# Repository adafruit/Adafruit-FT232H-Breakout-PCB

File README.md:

## Adafruit FT232H Breakout PCB
<a href="http://www.adafruit.com/products/2264"><br/>
Click here to purchase one from the Adafruit shop</a>

Wouldn't it be cool to drive a tiny OLED display, read a color sensor, or even just flash some LEDs directly from your computer?  Sure you can program an Arduino or Trinket to talk to these devices and your computer, but why can't your computer just talk to those devices and sensors itself?  Well, now your computer can talk to devices using the Adafruit FT232H breakout board!

What can the FT232H chip do?  This chip from FTDI is similar to their USB to serial converter chips but adds a 'multi-protocol synchronous serial engine' which allows it to speak many common protocols like SPI, I2C, serial UART, JTAG, and more!  There's even a handful of digital GPIO pins that you can read and write to do things like flash LEDs, read switches or buttons, and more.  The FT232H breakout is like adding a little swiss army knife for serial protocols to your computer!

PCB files for the Adafruit FT232H Breakout. The format is EagleCAD schematic and board layout
- http://www.adafruit.com/products/2264

### License

Adafruit invests time and resources providing this open source design, please support Adafruit and open-source hardware by purchasing products from [Adafruit](https://www.adafruit.com)!

All text above must be included in any redistribution

Designed by Limor Fried/Ladyada for Adafruit Industries.
Creative Commons Attribution/Share-Alike, all text above must be included in any redistribution. 
See license.txt for additional information.

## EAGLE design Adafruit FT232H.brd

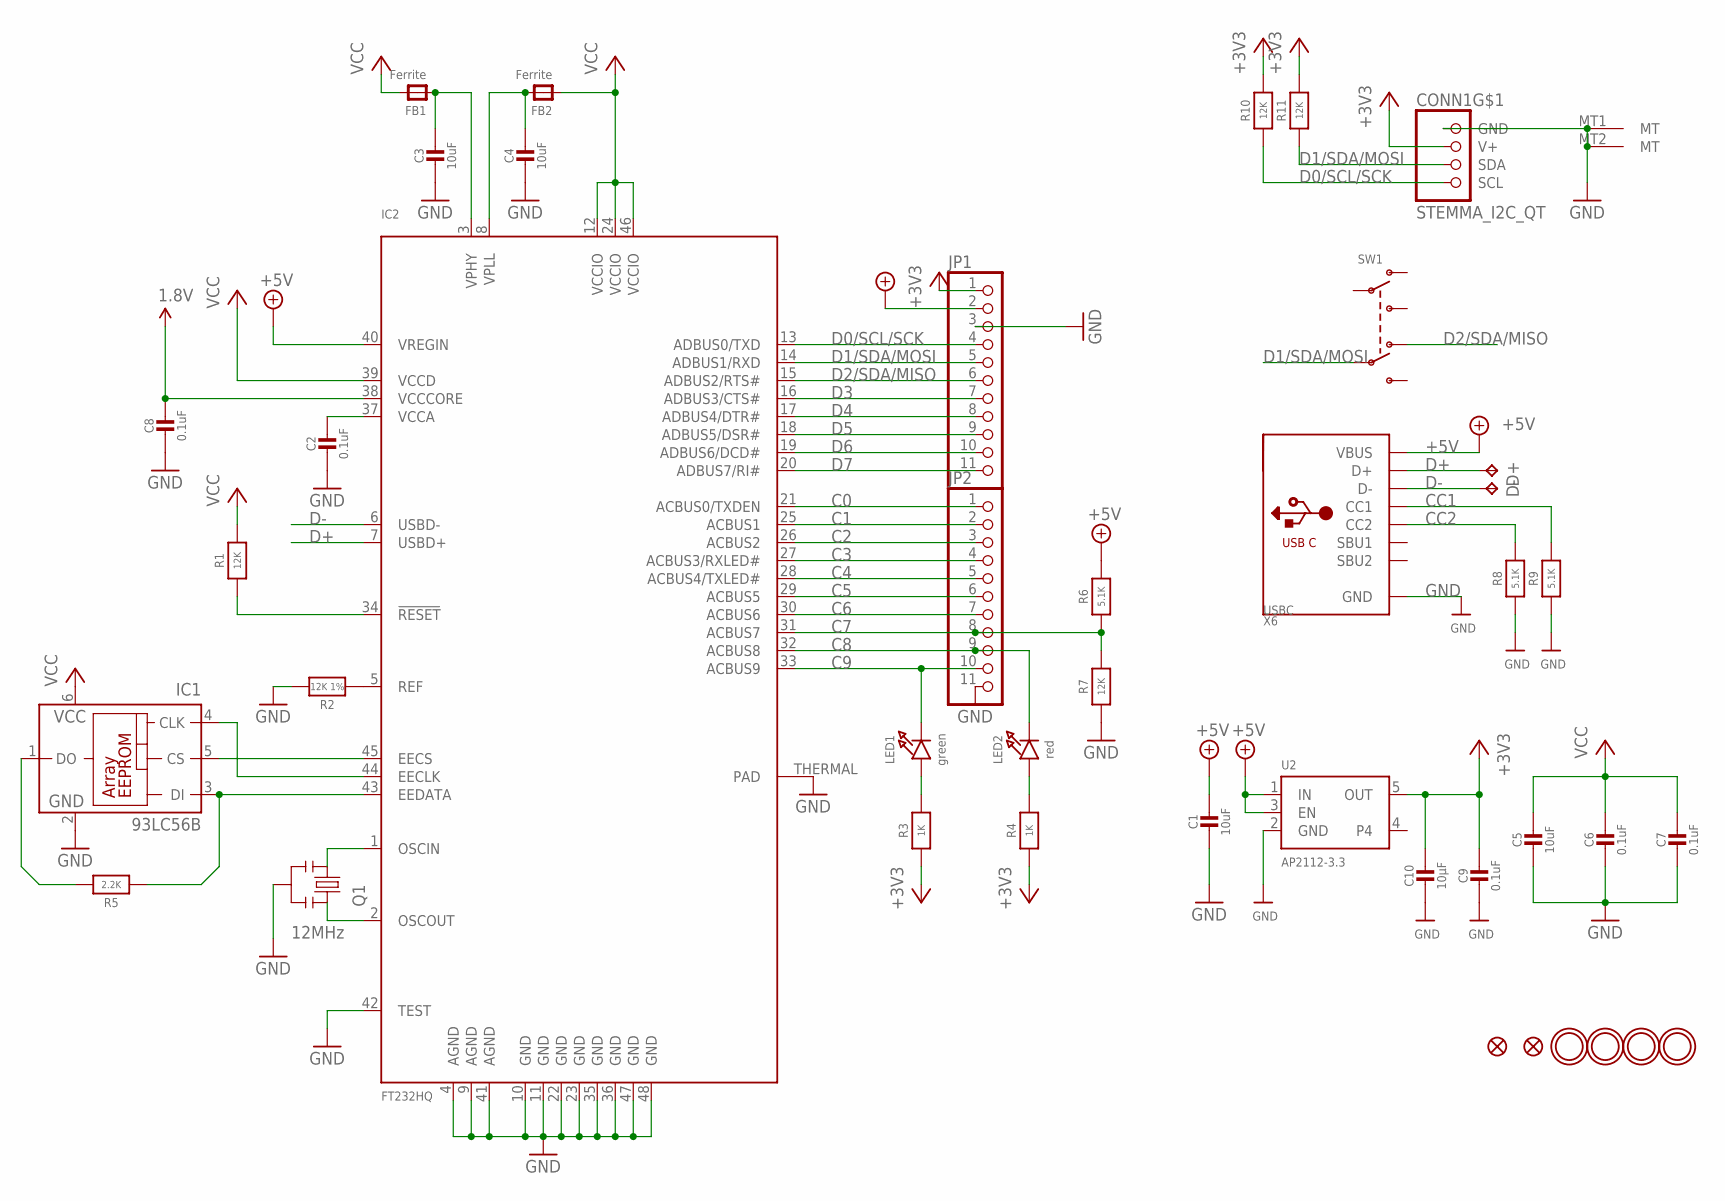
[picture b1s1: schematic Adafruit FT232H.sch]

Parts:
C1, C3, C4, C5: 10uF; 0805-NO
C2, C6, C7, C8, C9: 0.1uF; 0603-NO
C10: 10µF; 0805-NO
CONN1: STEMMA_I2C_QT; JST_SH4
D+: TPTP17R; TP17R
D-: TPTP17R; TP17R
FB1, FB2: Ferrite; _0805
FID1, FID2: FIDUCIAL""; FIDUCIAL_1MM
IC1: 93LC56B; SOT23-6
IC2: FT232HQ; QFN48_8MM
JP1, JP2: HEADER-1X11; 1X11_ROUND
LED1: green; CHIPLED_0805_NOOUTLINE
LED2: red; CHIPLED_0805_NOOUTLINE
Q1: 12MHz; RESONATOR-SMD
R1, R7, R10, R11: 12K; 0603-NO
R2: 12K 1%; 0603-NO
R3, R4: 1K; 0603-NO
R5: 2.2K; 0603-NO
R6, R8, R9: 5.1K; 0603-NO
SW1: SWITCH_DPDTEG1390; EG1390
U2: AP2112-3.3; SOT23-5
U$4, U$5, U$6, U$7: MOUNTINGHOLE2.5; MOUNTINGHOLE_2.5_PLATED
X6: USBC; USB_C_CUSB31-CFM2AX-01-X

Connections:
1.8V: C8.1, IC2.38 (VCCCORE)
+3V3: C9.1, C10.1, CONN1.2 (V+), JP1.1, R3.1, R4.1, R10.2, R11.2, U2.5 (OUT)
+5V: C1.1, IC2.40 (VREGIN), JP1.2, R6.2, U2.1 (IN), U2.3 (EN), X6.A4B9 (VBUS), X6.B4A9 (VBUS)
C0: IC2.21 (ACBUS0/TXDEN), JP2.1
C1: IC2.25 (ACBUS1), JP2.2
C2: IC2.26 (ACBUS2), JP2.3
C3: IC2.27 (ACBUS3/RXLED#), JP2.4
C4: IC2.28 (ACBUS4/TXLED#), JP2.5
C5: IC2.29 (ACBUS5), JP2.6
C6: IC2.30 (ACBUS6), JP2.7
C7: IC2.31 (ACBUS7), JP2.8, R6.1, R7.2
C8: IC2.32 (ACBUS8), JP2.9, LED2.C
C9: IC2.33 (ACBUS9), JP2.10, LED1.C
CC1: R9.2, X6.A5 (CC1)
CC2: R8.2, X6.B5 (CC2)
D0/SCL/SCK: CONN1.4 (SCL), IC2.13 (ADBUS0/TXD), JP1.4, R10.1
D1/SDA/MOSI: CONN1.3 (SDA), IC2.14 (ADBUS1/RXD), JP1.5, R11.1, SW1.P2
D2/SDA/MISO: IC2.15 (ADBUS2/RTS#), JP1.6, SW1.O2
D3: IC2.16 (ADBUS3/CTS#), JP1.7
D4: IC2.17 (ADBUS4/DTR#), JP1.8
D5: IC2.18 (ADBUS5/DSR#), JP1.9
D6: IC2.19 (ADBUS6/DCD#), JP1.10
D7: IC2.20 (ADBUS7/RI#), JP1.11
D+: D+.TP, IC2.7 (USBD+), X6.A6 (D+), X6.B6 (D+)
D-: D-.TP, IC2.6 (USBD-), X6.A7 (D-), X6.B7 (D-)
GND: C1.2, C2.2, C3.2, C4.2, C5.2, C6.2, C7.2, C8.2, C9.2, C10.2, CONN1.1 (GND), CONN1.MT1 (MT), CONN1.MT2 (MT), IC1.2 (GND), IC2.4 (AGND), IC2.9 (AGND), IC2.10 (GND), IC2.11 (GND), IC2.22 (GND), IC2.23 (GND), IC2.35 (GND), IC2.36 (GND), IC2.41 (AGND), IC2.42 (TEST), IC2.47 (GND), IC2.48 (GND), IC2.THERMAL (PAD), JP1.3, JP2.11, Q1.2, R2.2, R7.1, R8.1, R9.1, U2.2 (GND), X6.A1B12 (GND), X6.B1A12 (GND)
unnamed: IC2.1 (OSCIN), Q1.1
unnamed: IC2.2 (OSCOUT), Q1.3
unnamed: IC2.5 (REF), R2.1
unnamed: LED2.A, R4.2
unnamed: IC2.34 (!RESET), R1.1
unnamed: LED1.A, R3.2
unnamed: IC1.3 (DI), IC2.43 (EEDATA), R5.1
unnamed: IC1.5 (CS), IC2.45 (EECS)
unnamed: IC1.4 (CLK), IC2.44 (EECLK)
unnamed: IC1.1 (DO), R5.2
VCC: C5.1, C6.1, C7.1, FB1.2, FB2.1, IC1.6 (VCC), IC2.12 (VCCIO), IC2.24 (VCCIO), IC2.39 (VCCD), IC2.46 (VCCIO), R1.2
VCCA: C2.1, IC2.37 (VCCA)
VPHY: C3.1, FB1.1, IC2.3 (VPHY)
VPLL: C4.1, FB2.2, IC2.8 (VPLL)

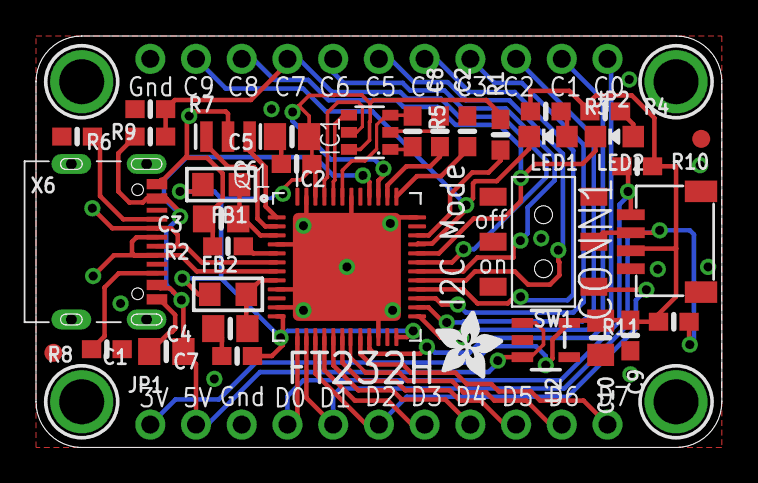
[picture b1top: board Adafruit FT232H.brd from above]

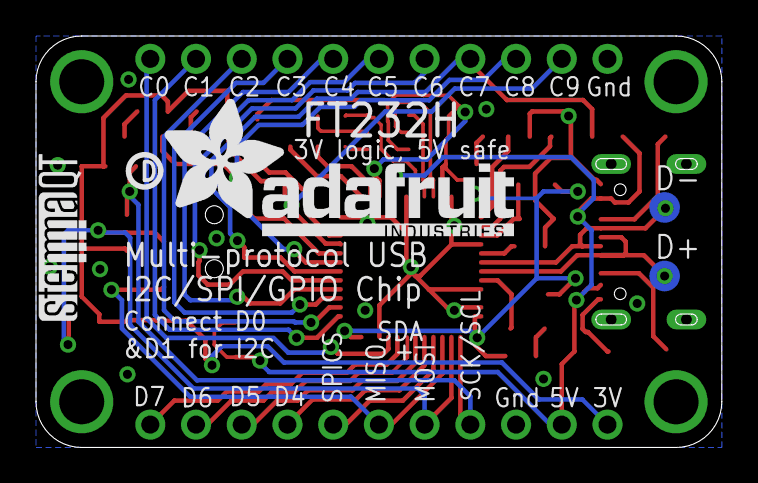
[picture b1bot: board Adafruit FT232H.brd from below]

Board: 2 copper layers, 38.1 x 22.9 mm, 46 parts (5 on the bottom side), 40 nets.

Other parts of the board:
U$2: ADAFRUIT_3.5MM
U$3: ADAFRUIT_TEXT_20MM
U$8: STEMMAQT
U$11: PCBFEAT-REV-040

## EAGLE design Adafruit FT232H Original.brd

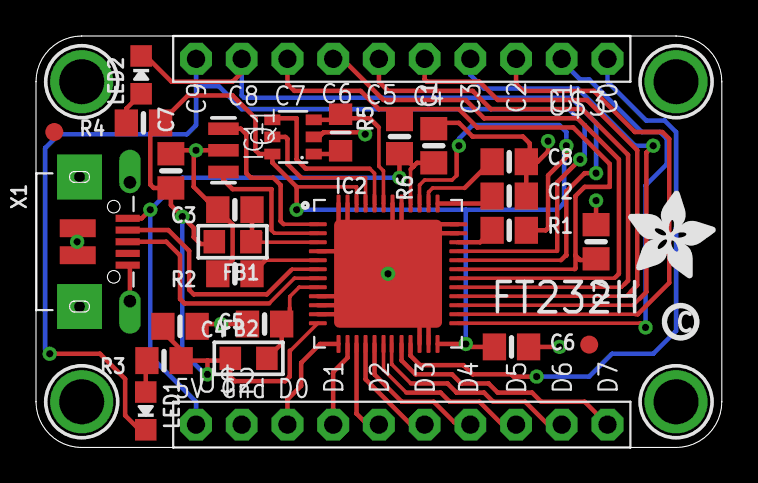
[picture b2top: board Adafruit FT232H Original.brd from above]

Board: 2 copper layers, 38.1 x 22.9 mm, 34 parts (1 on the bottom side), 37 nets.

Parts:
C1, C3, C4, C5: 10uF; 0805-NO
C2, C6, C7, C8: 0.1uF; 0805-NO
FB1, FB2: Ferrite; _0805
FID1, FID2: FIDUCIAL""; FIDUCIAL_1MM
IC1: 93LC56B; SOT23-6
IC2: FT232HQ; QFN48_8MM
LED1: green; CHIPLED_0805_NOOUTLINE
LED2: red; CHIPLED_0805_NOOUTLINE
Q1: CSTCR 12MHz; RESONATOR-SMD
R1, R7: 12K; 0805-NO
R2: 12K 1%; 0805-NO
R3, R4: 1K; 0805-NO
R5: 2.2K; _0805MP
R6: 4.7K; 0805-NO
U$2, U$3: PINHD-1X10; 1X10-BIG
U$4, U$5, U$6, U$7: MOUNTINGHOLE2.5; MOUNTINGHOLE_2.5_PLATED
U$8: ADAFRUIT_5MM
U$9: ADAFRUIT_TEXT_30MM
U$11: PCBFEAT-REV-040
X1: MiniB; 4UCONN_20329

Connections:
1.8V: C8.1, IC2.38
+3V3: C5.1, C6.1, C7.1, FB1.2, FB2.1, IC1.6, IC2.12, IC2.24, IC2.39, IC2.46, R1.2, R3.1, R4.1
+5V: C1.1, IC2.40, R6.2, U$2.1, X1.VBUS
C0: IC2.21, U$3.1
C1: IC2.25, U$3.2
C2: IC2.26, U$3.3
C3: IC2.27, U$3.4
C4: IC2.28, U$3.5
C5: IC2.29, U$3.6
C6: IC2.30, U$3.7
C7: IC2.31, R6.1, R7.2, U$3.8
C8: IC2.32, LED2.C, U$3.9
C9: IC2.33, LED1.C, U$3.10
D0: IC2.13, U$2.3
D1: IC2.14, U$2.4
D2: IC2.15, U$2.5
D3: IC2.16, U$2.6
D4: IC2.17, U$2.7
D5: IC2.18, U$2.8
D6: IC2.19, U$2.9
D7: IC2.20, U$2.10
D+: IC2.7, X1.D+
D-: IC2.6, X1.D-
GND: C1.2, C2.2, C3.2, C4.2, C5.2, C6.2, C7.2, C8.2, IC1.2, IC2.4, IC2.9, IC2.10, IC2.11, IC2.22, IC2.23, IC2.35, IC2.36, IC2.41, IC2.42, IC2.47, IC2.48, IC2.THERMAL, Q1.2, R2.2, R7.1, U$2.2, X1.BASE@1, X1.BASE@2, X1.GND, X1.SPRT@1, X1.SPRT@2, X1.SPRT@3, X1.SPRT@4
unnamed: IC2.1, Q1.1
unnamed: IC2.2, Q1.3
unnamed: IC2.5, R2.1
unnamed: LED2.A, R4.2
unnamed: IC2.34, R1.1
unnamed: LED1.A, R3.2
unnamed: IC1.3, IC2.43, R5.1
unnamed: IC1.5, IC2.45
unnamed: IC1.4, IC2.44
unnamed: IC1.1, R5.2
VCCA: C2.1, IC2.37
VPHY: C3.1, FB1.1, IC2.3
VPLL: C4.1, FB2.2, IC2.8

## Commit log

2016-07-19 init
2020-02-12 Rename file.
2020-02-12 create folder for image upload.
2020-02-12 Add product image.
2020-02-12 Add updated board files.

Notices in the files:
parts and their libraries:
microbuilder: This work is placed in the public domain, and may be freely used for commercial and non-commercial work with the following conditions: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
SparkFun: Licensing: CC v3.0 Share-Alike You are welcome to use this library for commercial purposes.
